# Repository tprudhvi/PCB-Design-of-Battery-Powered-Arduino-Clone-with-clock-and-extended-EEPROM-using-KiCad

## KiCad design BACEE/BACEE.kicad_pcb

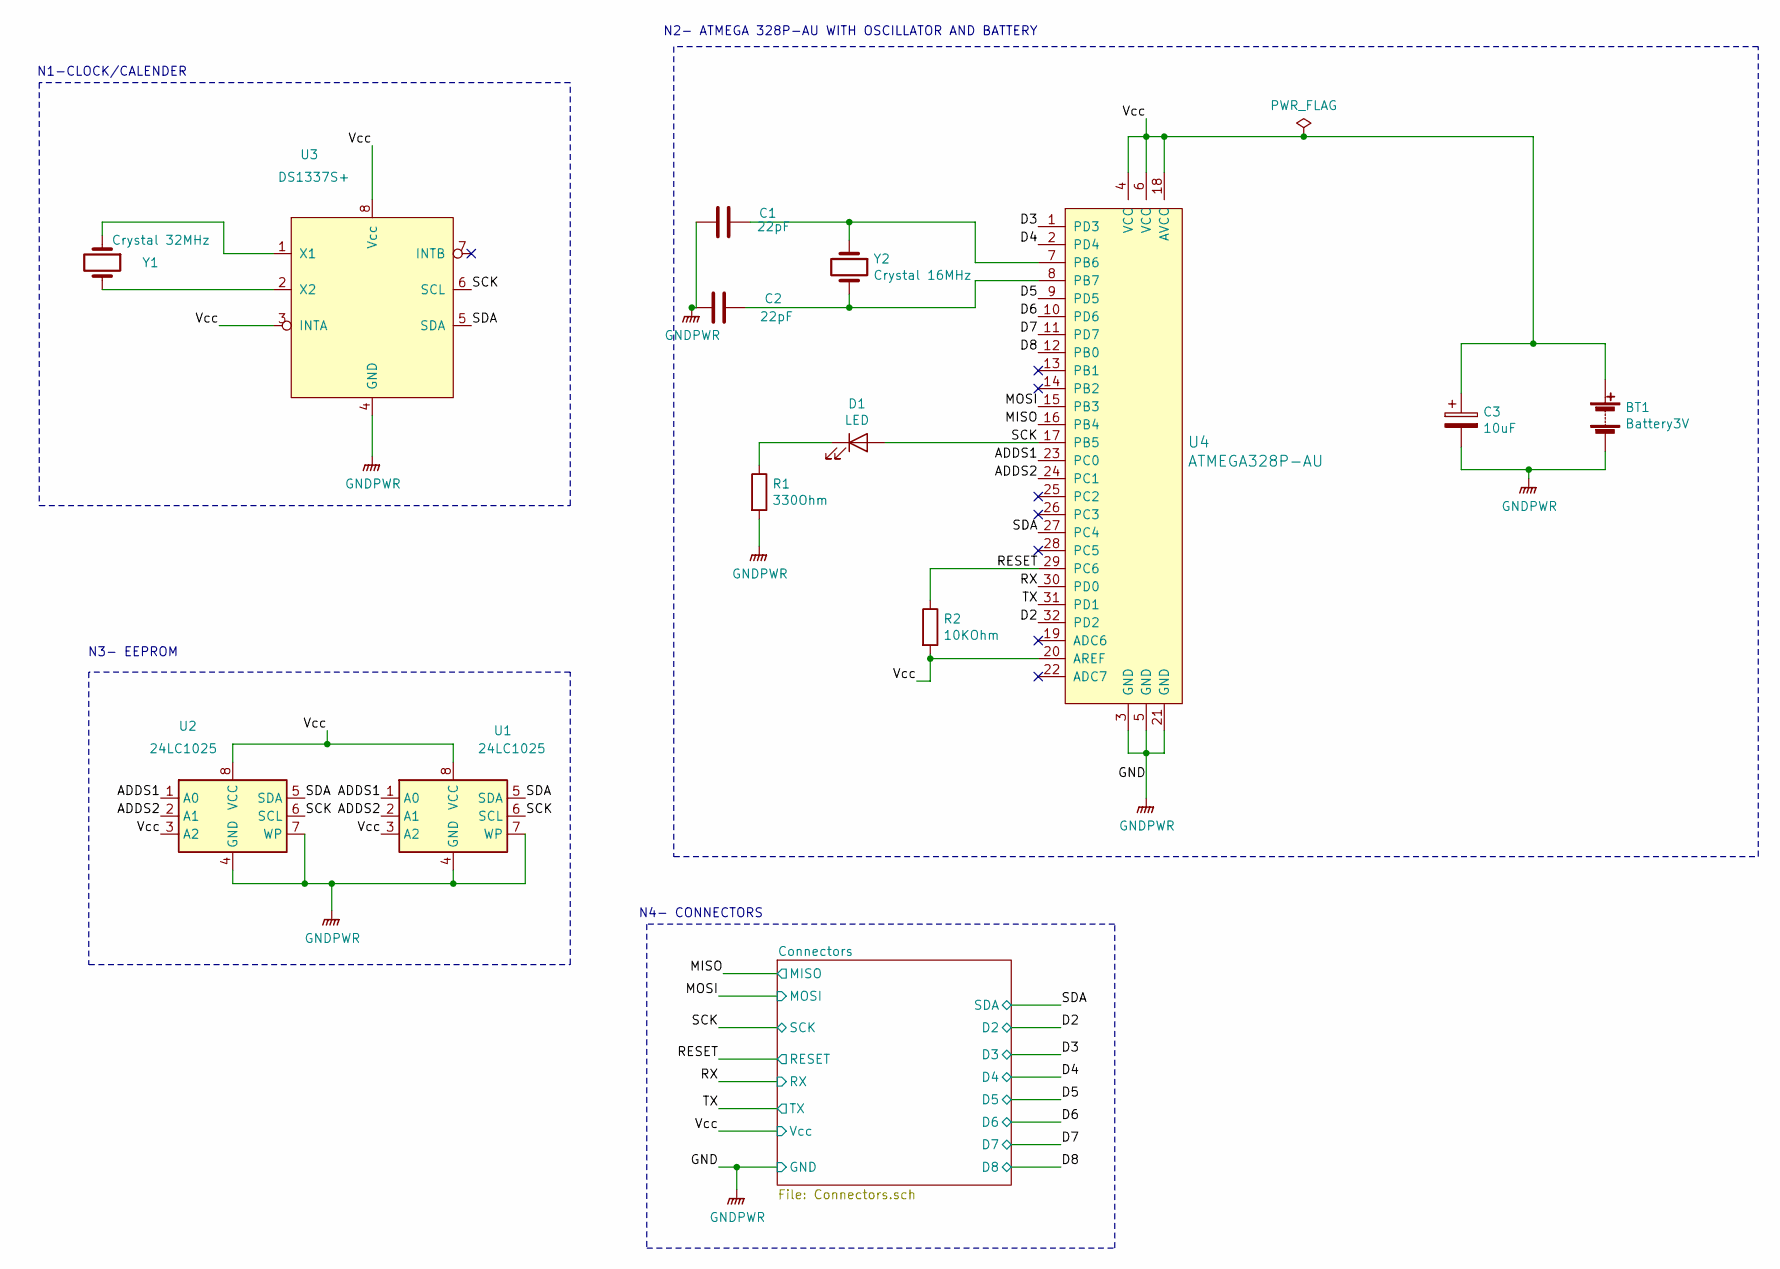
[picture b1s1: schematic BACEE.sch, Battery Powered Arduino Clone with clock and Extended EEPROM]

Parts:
BT1: Battery3V; PinSocket_1x02_P2.54mm_Vertical
C1, C2: 22pF; C_0805_2012Metric_Pad1.15x1.40mm_HandSolder
C3: 10uF; C_0805_2012Metric_Pad1.15x1.40mm_HandSolder
D1: LED; LED_0805_2012Metric_Pad1.15x1.40mm_HandSolder
R1: 330Ohm; R_0805_2012Metric_Pad1.15x1.40mm_HandSolder
R2: 10KOhm; R_0805_2012Metric_Pad1.15x1.40mm_HandSolder
U1, U2: 24LC1025; SOIJ-8_5.3x5.3mm_P1.27mm
U3: DS1337S+; SO-8_5.3x6.2mm_P1.27mm
U4: ATMEGA328P-AU; TQFP-32_7x7mm; MPN ATMEGA328P-AU; Digi-Key_PN ATMEGA328P-AU-ND
Y1: Crystal 32MHz; Crystal_SMD_MicroCrystal_CC7V-T1A-2Pin_3.2x1.5mm
Y2: Crystal 16MHz; Crystal_SMD_5032-2Pin_5.0x3.2mm_HandSoldering

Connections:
/ADDS1: U1.1 (A0), U2.1 (A0), U4.23 (PC0)
/ADDS2: U1.2 (A1), U2.2 (A1), U4.24 (PC1)
/D2: U4.32 (PD2); also elsewhere on the board
/D3: U4.1 (PD3); also elsewhere on the board
/D4: U4.2 (PD4); also elsewhere on the board
/D5: U4.9 (PD5); also elsewhere on the board
/D6: U4.10 (PD6); also elsewhere on the board
/D7: U4.11 (PD7); also elsewhere on the board
/D8: U4.12 (PB0); also elsewhere on the board
/MISO: U4.16 (PB4); also elsewhere on the board
/MOSI: U4.15 (PB3); also elsewhere on the board
/RESET: R2.1, U4.29 (PC6); also elsewhere on the board
/RX: U4.30 (PD0); also elsewhere on the board
/SCK: D1.2 (A), U1.6 (SCL), U2.6 (SCL), U3.6 (SCL), U4.17 (PB5); also elsewhere on the board
/SDA: U1.5 (SDA), U2.5 (SDA), U3.5 (SDA), U4.27 (PC4); also elsewhere on the board
/TX: U4.31 (PD1); also elsewhere on the board
/Vcc: BT1.1 (+), C3.1, R2.2, U1.3 (A2), U1.8 (VCC), U2.3 (A2), U2.8 (VCC), U3.3 (INTA), U3.8 (Vcc), U4.4 (VCC), U4.6 (VCC), U4.18 (AVCC), U4.20 (AREF); also elsewhere on the board
GNDPWR: BT1.2 (-), C1.1, C2.2, C3.2, R1.2, U1.4 (GND), U1.7 (WP), U2.4 (GND), U2.7 (WP), U3.4 (GND), U4.3 (GND), U4.5 (GND), U4.21 (GND); also elsewhere on the board
unnamed: C1.2, U4.7 (PB6), Y2.1
unnamed: C2.1, U4.8 (PB7), Y2.2
unnamed: D1.1 (K), R1.1
unnamed: U3.1 (X1), Y1.1
unnamed: U3.2 (X2), Y1.2

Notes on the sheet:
N1-CLOCK/CALENDER
N3- EEPROM
N2- ATMEGA 328P-AU WITH OSCILLATOR AND BATTERY
N4- CONNECTORS

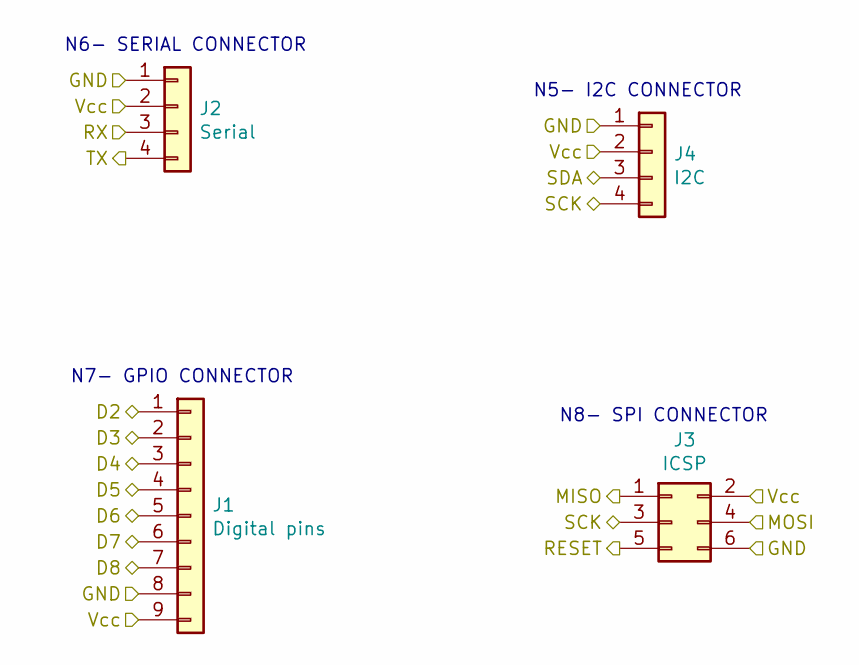
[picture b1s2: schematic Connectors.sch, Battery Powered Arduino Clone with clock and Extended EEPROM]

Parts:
J1: Digital pins; PinSocket_1x09_P2.54mm_Vertical
J2: Serial; PinSocket_1x04_P2.54mm_Vertical
J3: ICSP; PinSocket_2x03_P2.54mm_Vertical
J4: I2C; PinSocket_1x04_P2.54mm_Vertical

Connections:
/D2: J1.1; also elsewhere on the board
/D3: J1.2; also elsewhere on the board
/D4: J1.3; also elsewhere on the board
/D5: J1.4; also elsewhere on the board
/D6: J1.5; also elsewhere on the board
/D7: J1.6; also elsewhere on the board
/D8: J1.7; also elsewhere on the board
/MISO: J3.1; also elsewhere on the board
/MOSI: J3.4; also elsewhere on the board
/RESET: J3.5; also elsewhere on the board
/RX: J2.3; also elsewhere on the board
/SCK: J3.3, J4.4; also elsewhere on the board
/SDA: J4.3; also elsewhere on the board
/TX: J2.4; also elsewhere on the board
/Vcc: J1.9, J2.2, J3.2, J4.2; also elsewhere on the board
GNDPWR: J1.8, J2.1, J3.6, J4.1; also elsewhere on the board

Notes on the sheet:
N6- SERIAL CONNECTOR
N5- I2C CONNECTOR
N7- GPIO CONNECTOR
N8- SPI CONNECTOR

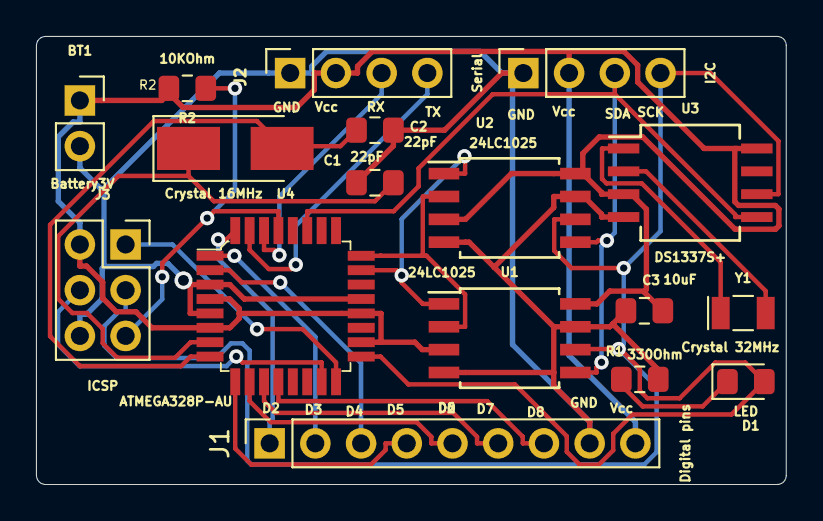
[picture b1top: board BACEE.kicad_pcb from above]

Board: 2 copper layers, 41.7 x 24.9 mm, 17 parts (0 on the bottom side), 23 nets.
